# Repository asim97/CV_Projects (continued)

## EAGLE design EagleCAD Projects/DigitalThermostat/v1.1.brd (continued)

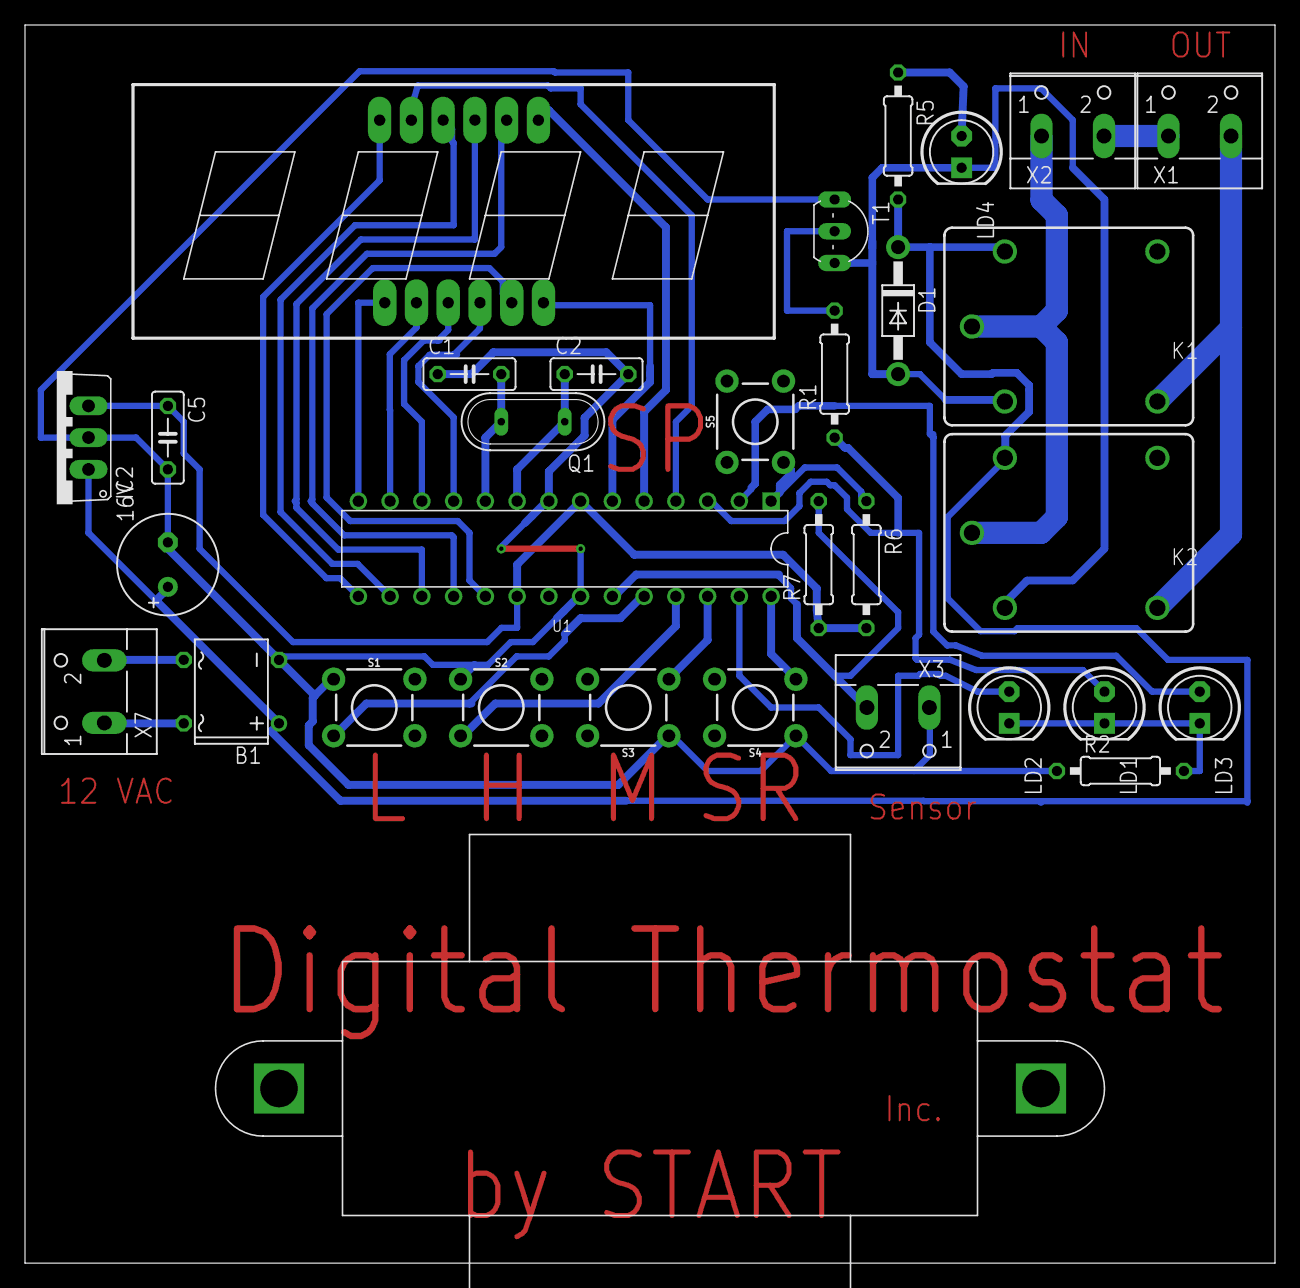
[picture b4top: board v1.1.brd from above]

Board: 2 copper layers, 100.0 x 99.0 mm, 32 parts (0 on the bottom side), 35 nets.

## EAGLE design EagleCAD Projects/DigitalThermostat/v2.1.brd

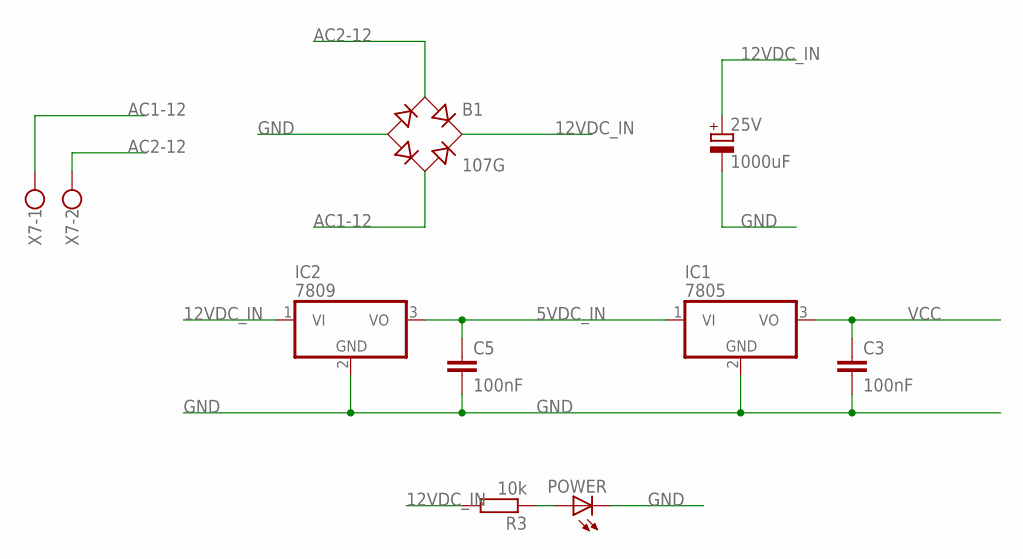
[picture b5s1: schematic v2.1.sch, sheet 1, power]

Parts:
25V: 1000uF; E3,5-8
B1: 107G; DB
C3, C5: 100nF; C050-025X075
IC1: 7805; TO220V
IC2: 7809; TO220V
POWER: LED5MM
R3: 10k; 0207/10
X7: W237-102

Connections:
5VDC_IN: C5.1, IC1.1 (VI), IC2.3 (VO)
12VDC_IN: 25V.+, B1.+, IC2.1 (VI), R3.2; also elsewhere on the board
AC1-12: B1.AC2, X7.1
AC2-12: B1.AC1, X7.2
GND: 25V.-, B1.-, C3.2, C5.2, IC1.2 (GND), IC2.2 (GND), POWER.K (C); also elsewhere on the board
unnamed: POWER.A, R3.1
VCC: C3.1, IC1.3 (VO); also elsewhere on the board

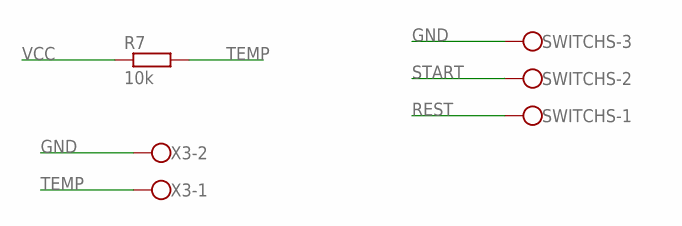
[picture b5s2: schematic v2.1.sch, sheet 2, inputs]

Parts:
R7: 10k; 0207/10
SWITCHS: W237-103
X3: W237-102

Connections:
GND: SWITCHS.3, X3.2; also elsewhere on the board
REST: SWITCHS.1; also elsewhere on the board
START: SWITCHS.2; also elsewhere on the board
TEMP: R7.2, X3.1; also elsewhere on the board
VCC: R7.1; also elsewhere on the board

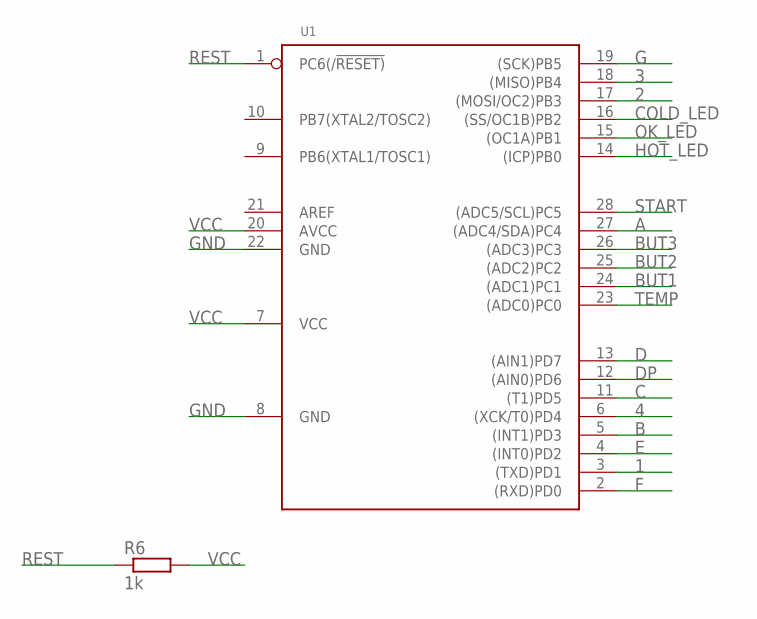
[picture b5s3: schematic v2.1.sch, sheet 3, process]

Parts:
R6: 1k; 0207/10
U1: MCU-ATMEGA328P-PU(DIP28); DIP28-2.54-34.7X7.62MM

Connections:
1: U1.3 ((TXD)PD1)
2: U1.17 ((MOSI/OC2)PB3)
3: U1.18 ((MISO)PB4)
4: U1.6 ((XCK/T0)PD4)
A: U1.27 ((ADC4/SDA)PC4)
B: U1.5 ((INT1)PD3)
BUT1: U1.24 ((ADC1)PC1)
BUT2: U1.25 ((ADC2)PC2)
BUT3: U1.26 ((ADC3)PC3)
C: U1.11 ((T1)PD5)
COLD_LED: U1.16 ((SS/OC1B)PB2); also elsewhere on the board
D: U1.13 ((AIN1)PD7)
DP: U1.12 ((AIN0)PD6)
E: U1.4 ((INT0)PD2)
F: U1.2 ((RXD)PD0)
G: U1.19 ((SCK)PB5)
GND: U1.8 (GND), U1.22 (GND); also elsewhere on the board
HOT_LED: U1.14 ((ICP)PB0); also elsewhere on the board
OK_LED: U1.15 ((OC1A)PB1); also elsewhere on the board
REST: R6.1, U1.1 (PC6(/!RESET)); also elsewhere on the board
START: U1.28 ((ADC5/SCL)PC5); also elsewhere on the board
TEMP: U1.23 ((ADC0)PC0); also elsewhere on the board
VCC: R6.2, U1.7 (VCC), U1.20 (AVCC); also elsewhere on the board

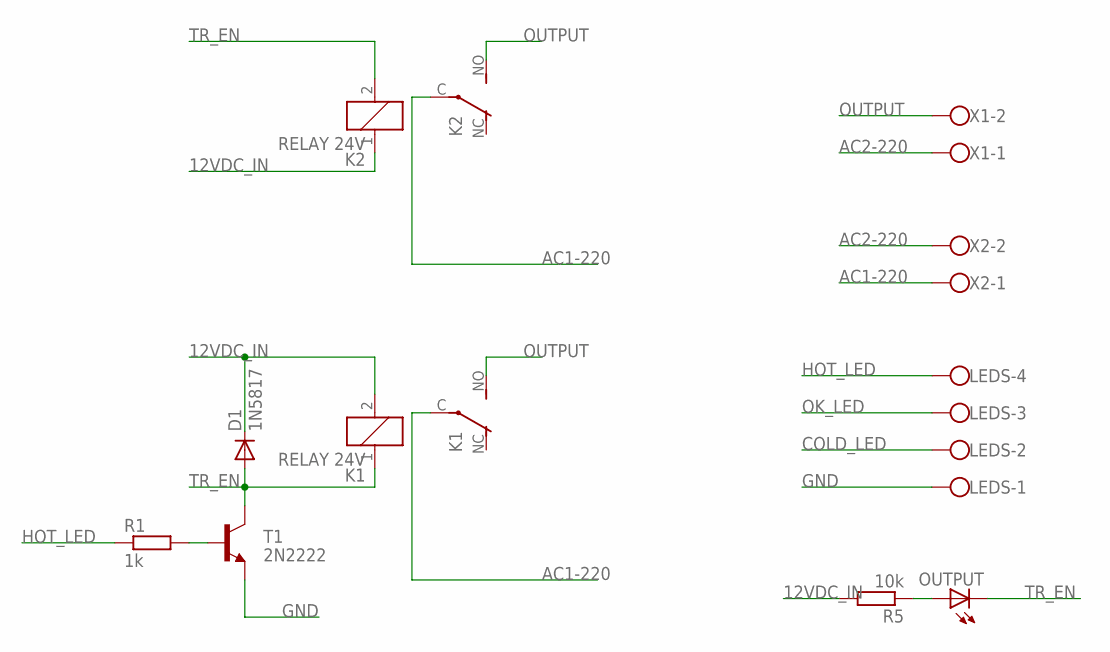
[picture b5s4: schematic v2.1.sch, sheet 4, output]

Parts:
D1: 1N5817; DO41-10
K1, K2: RELAY 24V; JS-M
LEDS: W237-4
OUTPUT: LED5MM
R1: 1k; 0207/10
R5: 10k; 0207/10
T1: 2N2222; TO92-EBC-OVAL
X1, X2: W237-102

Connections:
12VDC_IN: D1.C, K1.2, K2.1, R5.2; also elsewhere on the board
AC1-220: K1.C, K2.C, X2.1
AC2-220: X1.1, X2.2
COLD_LED: LEDS.2; also elsewhere on the board
GND: LEDS.1, T1.E; also elsewhere on the board
HOT_LED: LEDS.4, R1.1; also elsewhere on the board
unnamed: OUTPUT.A, R5.1
unnamed: R1.2, T1.B
OK_LED: LEDS.3; also elsewhere on the board
OUTPUT: K1.NO (S), K2.NO (S), X1.2
TR_EN: D1.A, K1.1, K2.2, OUTPUT.K (C), T1.C

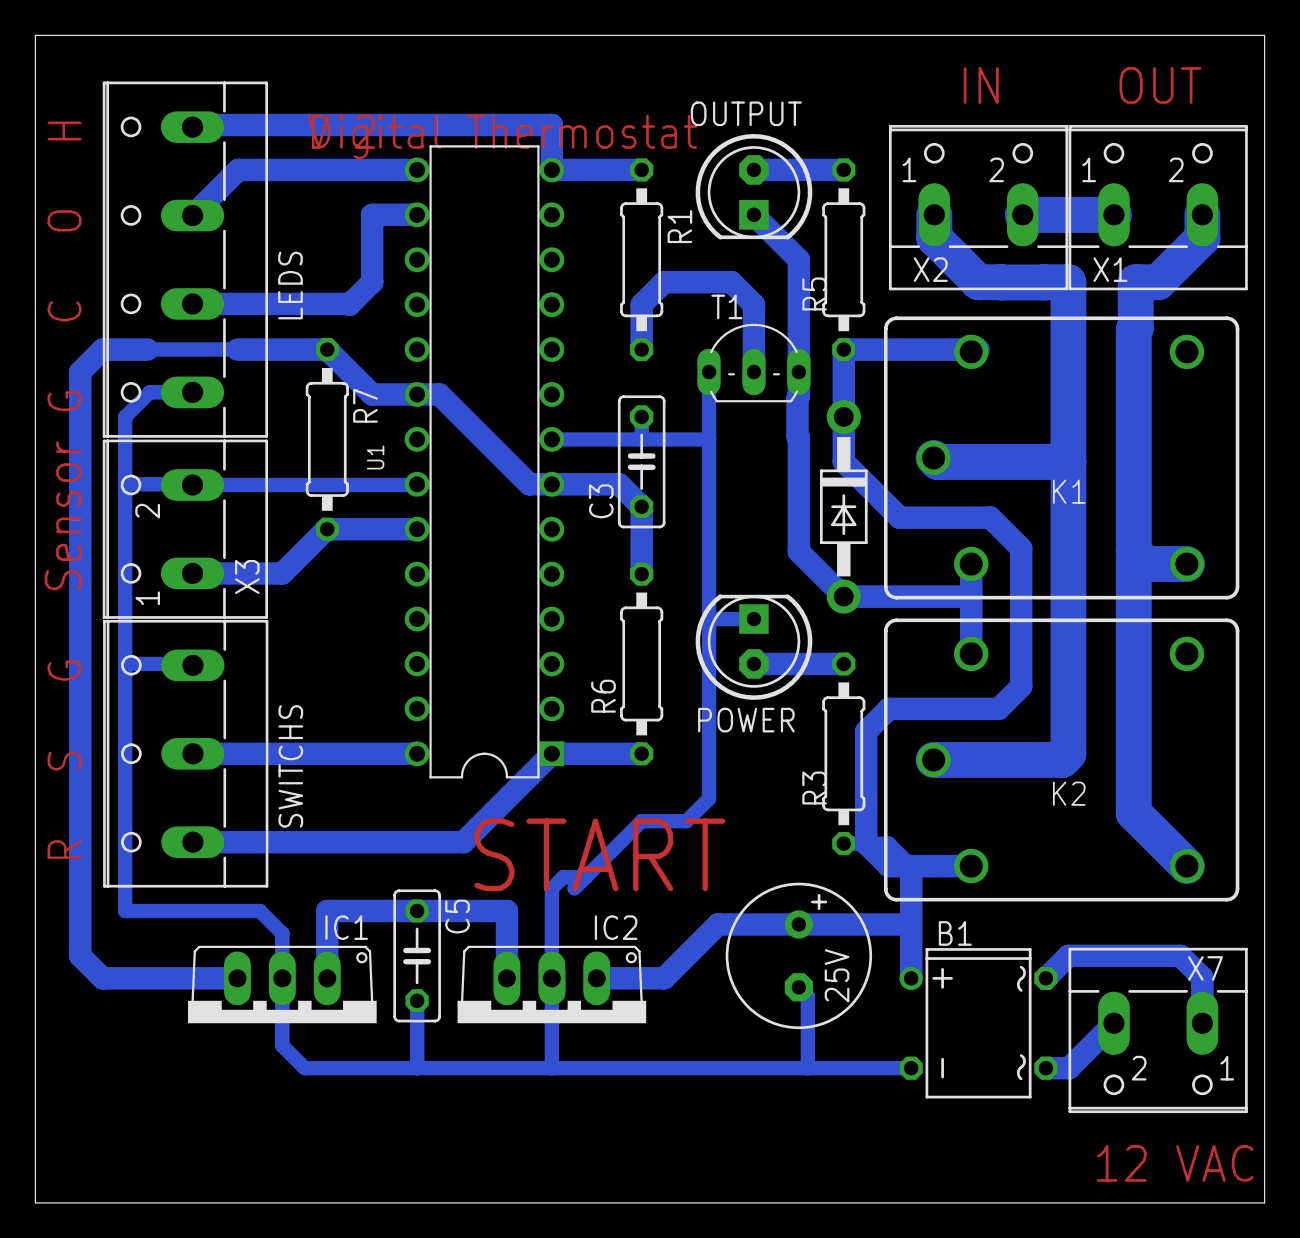
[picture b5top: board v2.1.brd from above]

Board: 2 copper layers, 69.5 x 66.0 mm, 24 parts (0 on the bottom side), 19 nets.

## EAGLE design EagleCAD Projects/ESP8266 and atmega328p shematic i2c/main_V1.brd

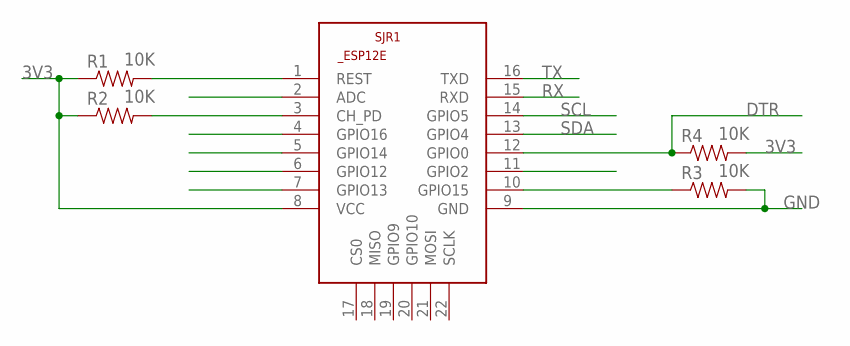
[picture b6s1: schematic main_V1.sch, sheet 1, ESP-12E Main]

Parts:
R1, R2, R3, R4: 10K; 1206
SJR1: ESP8266-12EESP12E; ESP8266-ESP12E

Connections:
3V3: R1.1, R2.1, R4.2, SJR1.8 (VCC); also elsewhere on the board
DTR: R4.1, SJR1.12 (GPIO0)
GND: R3.2, SJR1.9 (GND); also elsewhere on the board
unnamed: R1.2, SJR1.1 (REST)
unnamed: R2.2, SJR1.3 (CH_PD)
unnamed: R3.1, SJR1.10 (GPIO15)
RX: SJR1.15 (RXD)
SCL: SJR1.14 (GPIO5); also elsewhere on the board
SDA: SJR1.13 (GPIO4); also elsewhere on the board
TX: SJR1.16 (TXD)

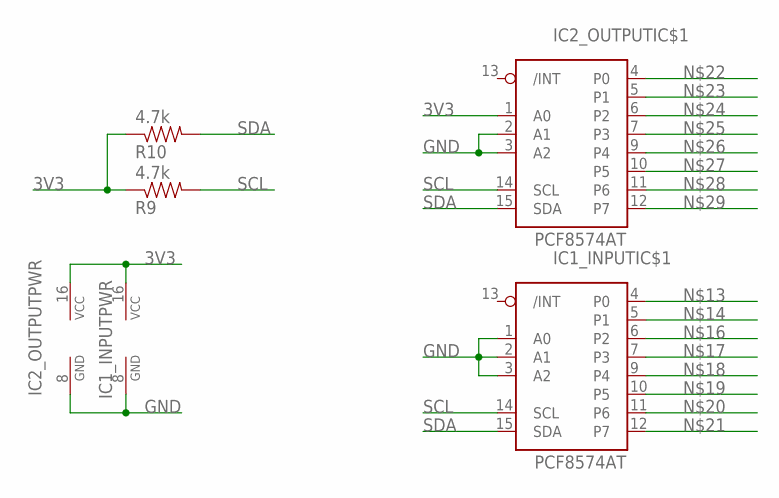
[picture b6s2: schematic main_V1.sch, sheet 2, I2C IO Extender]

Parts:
IC1_INPUT, IC2_OUTPUT: PCF8574AT; SO16
R9, R10: 4.7k; 1206

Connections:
3V3: IC1_INPUT.16 (VCC), IC2_OUTPUT.1 (A0), IC2_OUTPUT.16 (VCC), R9.1, R10.1; also elsewhere on the board
GND: IC1_INPUT.1 (A0), IC1_INPUT.2 (A1), IC1_INPUT.3 (A2), IC1_INPUT.8 (GND), IC2_OUTPUT.2 (A1), IC2_OUTPUT.3 (A2), IC2_OUTPUT.8 (GND); also elsewhere on the board
SCL: IC1_INPUT.14 (SCL), IC2_OUTPUT.14 (SCL), R9.2; also elsewhere on the board
SDA: IC1_INPUT.15 (SDA), IC2_OUTPUT.15 (SDA), R10.2; also elsewhere on the board

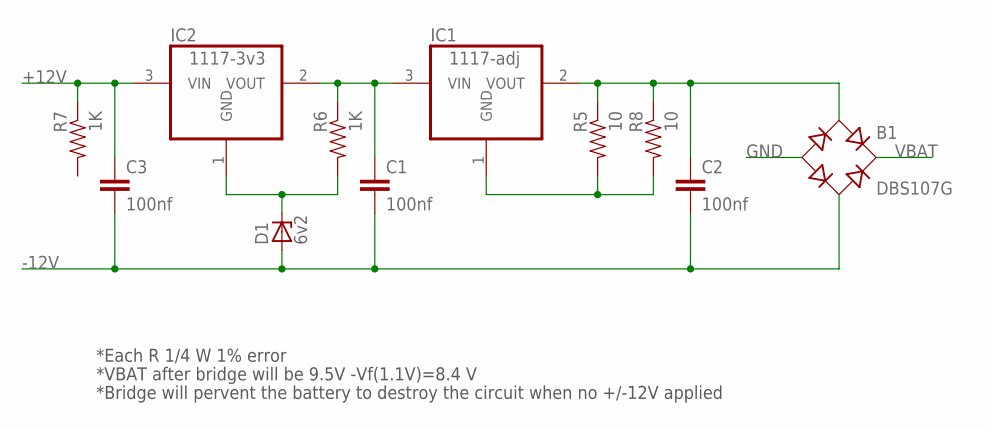
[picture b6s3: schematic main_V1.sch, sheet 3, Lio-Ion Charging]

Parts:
B1: DBS107G; DBS
C1, C2, C3: 100nf; C1206K
D1: 6v2; SOT23
IC1: 1117-adj; SOT223
IC2: 1117-3v3; SOT223
R5, R8: 10; 1206
R6, R7: 1K; 1206

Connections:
+12V: C3.1, IC2.3 (VIN), R7.1
-12V: B1.AC2, C1.2, C2.2, C3.2, D1.1 (A)
GND: B1.-; also elsewhere on the board
unnamed: D1.3 (C), IC2.1 (GND), R6.2
unnamed: IC1.1 (GND), R5.2, R8.2
unnamed: B1.AC1, C2.1, IC1.2 (VOUT), R5.1, R8.1
unnamed: C1.1, IC1.3 (VIN), IC2.2 (VOUT), R6.1
VBAT: B1.+; also elsewhere on the board

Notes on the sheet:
*Each R 1/4 W 1% error
*VBAT after bridge will be 9.5V -Vf(1.1V)=8.4 V
*Bridge will pervent the battery to destroy the circuit when no +/-12V applied

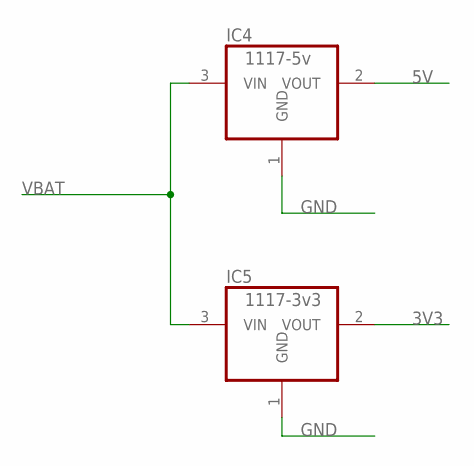
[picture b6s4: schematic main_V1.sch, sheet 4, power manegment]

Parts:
IC4: 1117-5v; SOT223
IC5: 1117-3v3; SOT223

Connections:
3V3: IC5.2 (VOUT); also elsewhere on the board
5V: IC4.2 (VOUT)
GND: IC4.1 (GND), IC5.1 (GND); also elsewhere on the board
VBAT: IC4.3 (VIN), IC5.3 (VIN); also elsewhere on the board

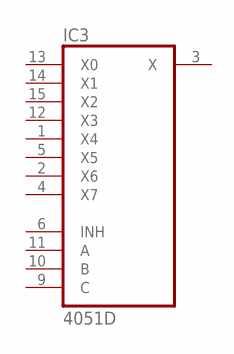
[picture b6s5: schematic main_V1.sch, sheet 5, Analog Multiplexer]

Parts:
IC3: 4051D; SO16

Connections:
GND: IC3.8 (GND); also elsewhere on the board
VCC: IC3.16 (VCC)
VEE: IC3.7 (VEE)

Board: 2 copper layers, 23 parts (0 on the bottom side), 15 nets, no tracks yet.
